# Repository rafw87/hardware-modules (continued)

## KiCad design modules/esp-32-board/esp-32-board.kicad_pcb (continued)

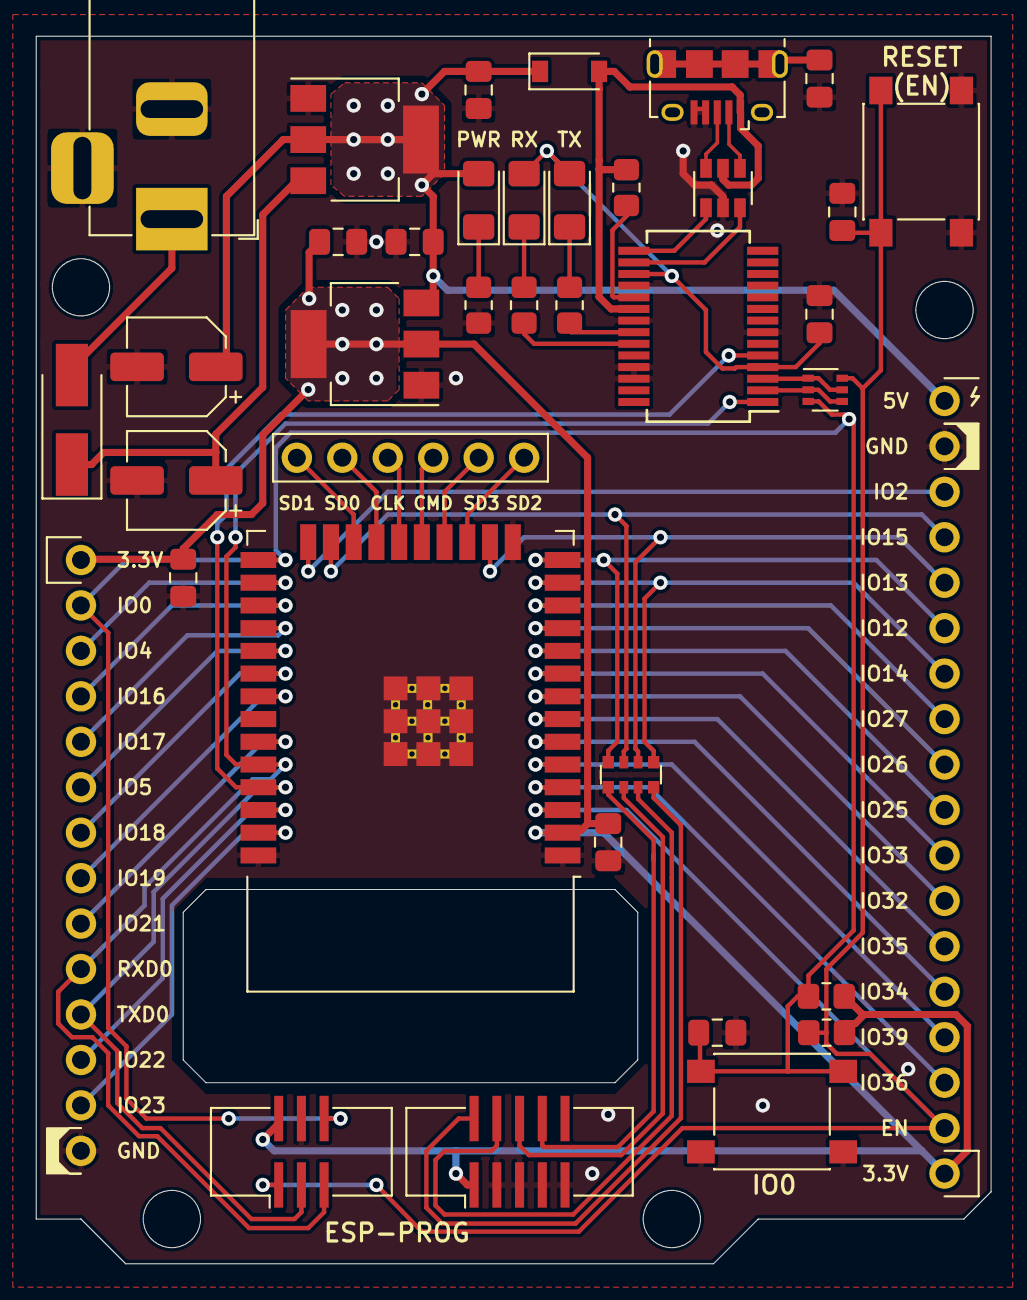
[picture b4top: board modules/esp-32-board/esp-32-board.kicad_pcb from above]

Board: 2 copper layers, 53.4 x 68.6 mm, 39 parts (0 on the bottom side), 57 nets.

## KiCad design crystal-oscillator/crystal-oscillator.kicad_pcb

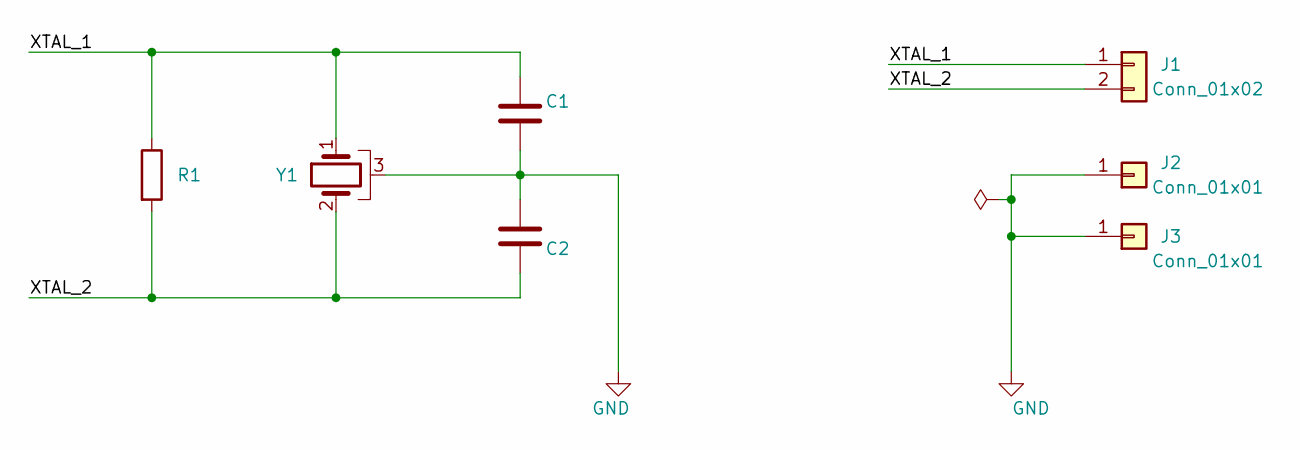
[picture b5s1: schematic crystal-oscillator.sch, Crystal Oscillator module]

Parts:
C1, C2: C; C_Disc_D3.4mm_W2.1mm_P2.50mm
J1: Conn_01x02; PinHeader_1x02_P2.54mm_Vertical
J2, J3: Conn_01x01; PinHeader_1x01_P2.54mm_Vertical-GND
R1: R; R_Axial_DIN0207_L6.3mm_D2.5mm_P7.62mm_Horizontal
Y1: Crystal_GND3; Crystal_C26-LF_D2.1mm_L6.5mm_Horizontal_1EP_style1

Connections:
/XTAL_1: C1.1, J1.1, R1.1, Y1.1
/XTAL_2: C2.2, J1.2, R1.2, Y1.2
GND: C1.2, C2.1, J2.1, J3.1, Y1.3

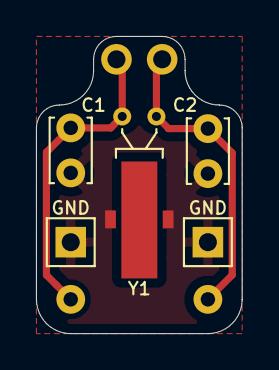
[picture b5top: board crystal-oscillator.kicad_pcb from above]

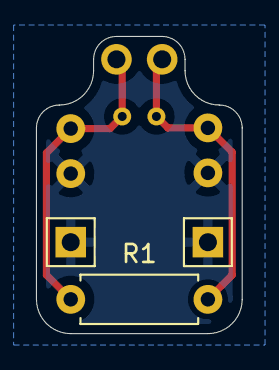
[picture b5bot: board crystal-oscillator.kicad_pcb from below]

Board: 2 copper layers, 11.4 x 16.5 mm, 7 parts (4 on the bottom side), 3 nets.

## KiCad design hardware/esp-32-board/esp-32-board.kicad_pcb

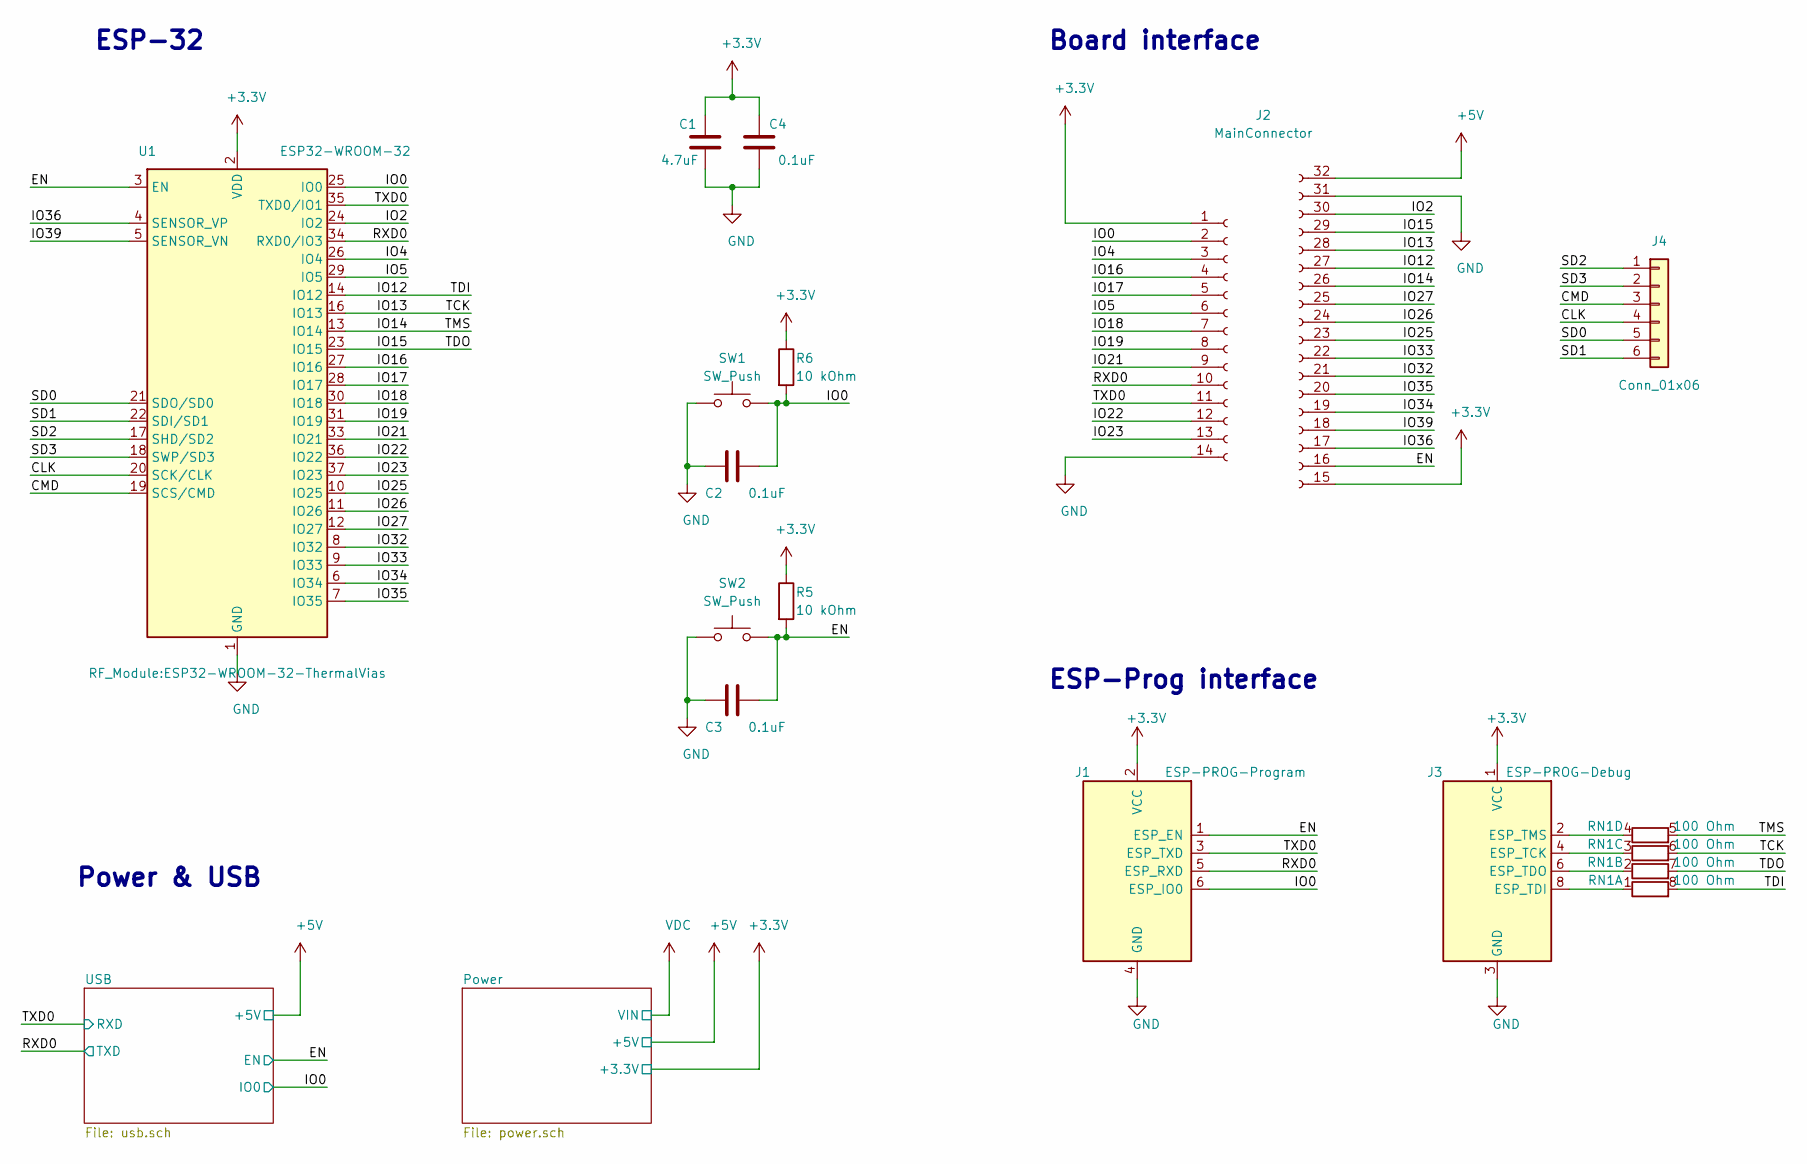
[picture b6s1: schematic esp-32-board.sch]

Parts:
C1: 4.7uF; C_0805_2012Metric_Pad1.18x1.45mm_HandSolder
C2, C3, C4: 0.1uF; C_0805_2012Metric_Pad1.18x1.45mm_HandSolder
J1: ESP-PROG-Program; IDC-Header_2x03_P1.27mm_Vertical_SMD
J2: MainConnector
J3: ESP-PROG-Debug; IDC-Header_2x05_P1.27mm_Vertical_SMD
J4: Conn_01x06; PinSocket_1x06_P2.54mm_Vertical
R5, R6: 10 kOhm; R_0805_2012Metric_Pad1.20x1.40mm_HandSolder
RN1: 100 Ohm; R_Array_Convex_4x0612
SW1, SW2: SW_Push; SW_Push_1P1T_NO_6x6mm_H4.3mm
U1: ESP32-WROOM-32; ESP32-WROOM-32-ThermalVias

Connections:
+3V3: C1.1, C4.1, J1.2 (VCC), J2.1, J2.15, J3.1 (VCC), R5.1, R6.1, U1.2 (VDD); also elsewhere on the board
+5V: J2.32; also elsewhere on the board
/CLK: J4.4, U1.20 (SCK/CLK)
/CMD: J4.3, U1.19 (SCS/CMD)
/EN: C3.2, J1.1 (ESP_EN), J2.16, R5.2, SW2.2, U1.3 (EN); also elsewhere on the board
/IO0: C2.2, J1.6 (ESP_IO0), J2.2, R6.2, SW1.2, U1.25 (IO0); also elsewhere on the board
/IO2: J2.30, U1.24 (IO2)
/IO4: J2.3, U1.26 (IO4)
/IO5: J2.6, U1.29 (IO5)
/IO12: J2.27, RN1.8 (R1.2), U1.14 (IO12)
/IO13: J2.28, RN1.6 (R3.2), U1.16 (IO13)
/IO14: J2.26, RN1.5 (R4.2), U1.13 (IO14)
/IO15: J2.29, RN1.7 (R2.2), U1.23 (IO15)
/IO16: J2.4, U1.27 (IO16)
/IO17: J2.5, U1.28 (IO17)
/IO18: J2.7, U1.30 (IO18)
/IO19: J2.8, U1.31 (IO19)
/IO21: J2.9, U1.33 (IO21)
/IO22: J2.12, U1.36 (IO22)
/IO23: J2.13, U1.37 (IO23)
/IO25: J2.23, U1.10 (IO25)
/IO26: J2.24, U1.11 (IO26)
/IO27: J2.25, U1.12 (IO27)
/IO32: J2.21, U1.8 (IO32)
/IO33: J2.22, U1.9 (IO33)
/IO34: J2.19, U1.6 (IO34)
/IO35: J2.20, U1.7 (IO35)
/IO36: J2.17, U1.4 (SENSOR_VP)
/IO39: J2.18, U1.5 (SENSOR_VN)
/RXD0: J1.5 (ESP_RXD), J2.10, U1.34 (RXD0/IO3); also elsewhere on the board
/SD0: J4.5, U1.21 (SDO/SD0)
/SD1: J4.6, U1.22 (SDI/SD1)
/SD2: J4.1, U1.17 (SHD/SD2)
/SD3: J4.2, U1.18 (SWP/SD3)
/TXD0: J1.3 (ESP_TXD), J2.11, U1.35 (TXD0/IO1); also elsewhere on the board
GND: C1.2, C2.1, C3.1, C4.2, J1.4 (GND), J2.14, J2.31, J3.3 (GND), J3.5 (GND), J3.7 (GND), J3.9 (GND), SW1.1, SW2.1, U1.1 (GND), U1.15 (GND), U1.38 (GND), U1.39 (GND); also elsewhere on the board
unnamed: J3.2 (ESP_TMS), RN1.4 (R4.1)
unnamed: J3.4 (ESP_TCK), RN1.3 (R3.1)
unnamed: J3.6 (ESP_TDO), RN1.2 (R2.1)
unnamed: J3.8 (ESP_TDI), RN1.1 (R1.1)

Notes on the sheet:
Power & USB
ESP-Prog interface
Board interface
ESP-32

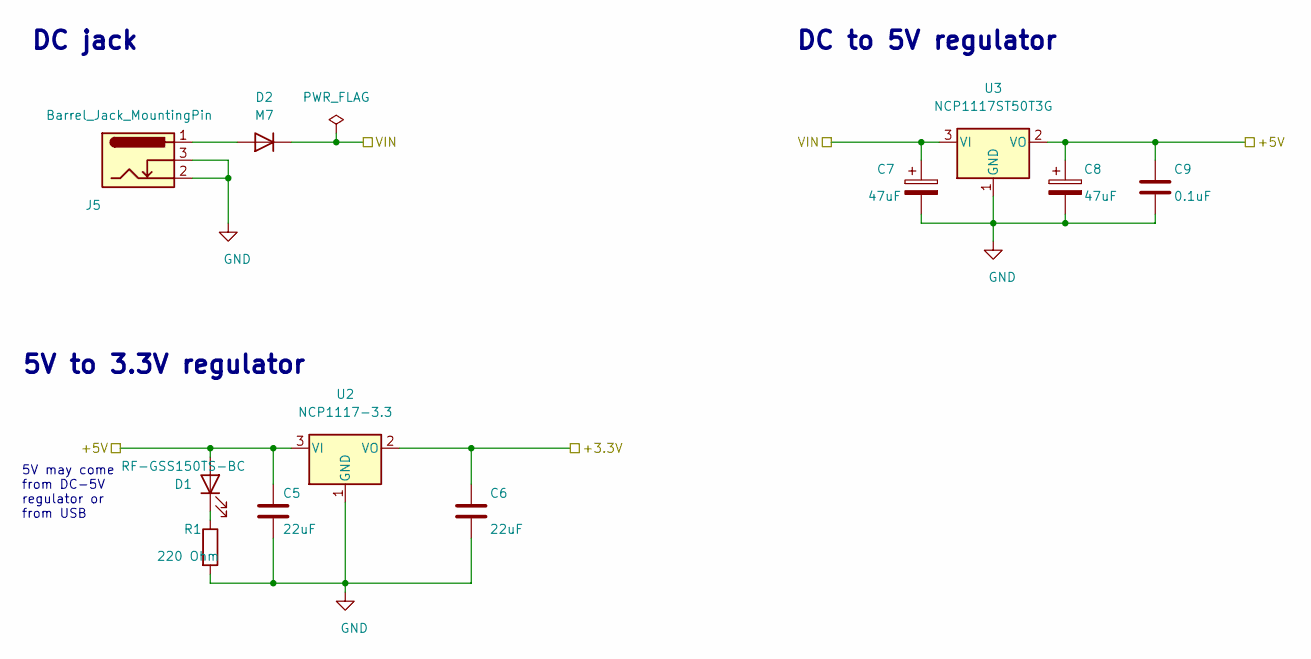
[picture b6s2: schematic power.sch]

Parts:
C5, C6: 22uF; C_0805_2012Metric_Pad1.18x1.45mm_HandSolder
C7, C8: 47uF; CP_Elec_5x5.9
C9: 0.1uF; C_0805_2012Metric_Pad1.18x1.45mm_HandSolder
D1: RF-GSS150TS-BC; LED_1206_3216Metric_Pad1.42x1.75mm_HandSolder
D2: M7; D_SMA_Handsoldering
J5: Barrel_Jack_MountingPin; BarrelJack_CLIFF_FC68148_Horizontal
R1: 220 Ohm; R_0805_2012Metric_Pad1.20x1.40mm_HandSolder
U2: NCP1117-3.3; SOT-223-3_TabPin2
U3: NCP1117ST50T3G; SOT-223-3_TabPin2

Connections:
+3V3: C6.1, U2.2 (VO); also elsewhere on the board
+5V: C5.1, C8.1, C9.1, D1.2 (A), U2.3 (VI), U3.2 (VO); also elsewhere on the board
GND: C5.2, C6.2, C7.2, C8.2, C9.2, J5.2, J5.3, R1.2, U2.1 (GND), U3.1 (GND); also elsewhere on the board
unnamed: D1.1 (K), R1.1
unnamed: D2.2 (A), J5.1
VDC: C7.1, D2.1 (K), U3.3 (VI)

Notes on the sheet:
DC jack
DC to 5V regulator
5V to 3.3V regulator
5V may come from DC-5V regulator or from USB

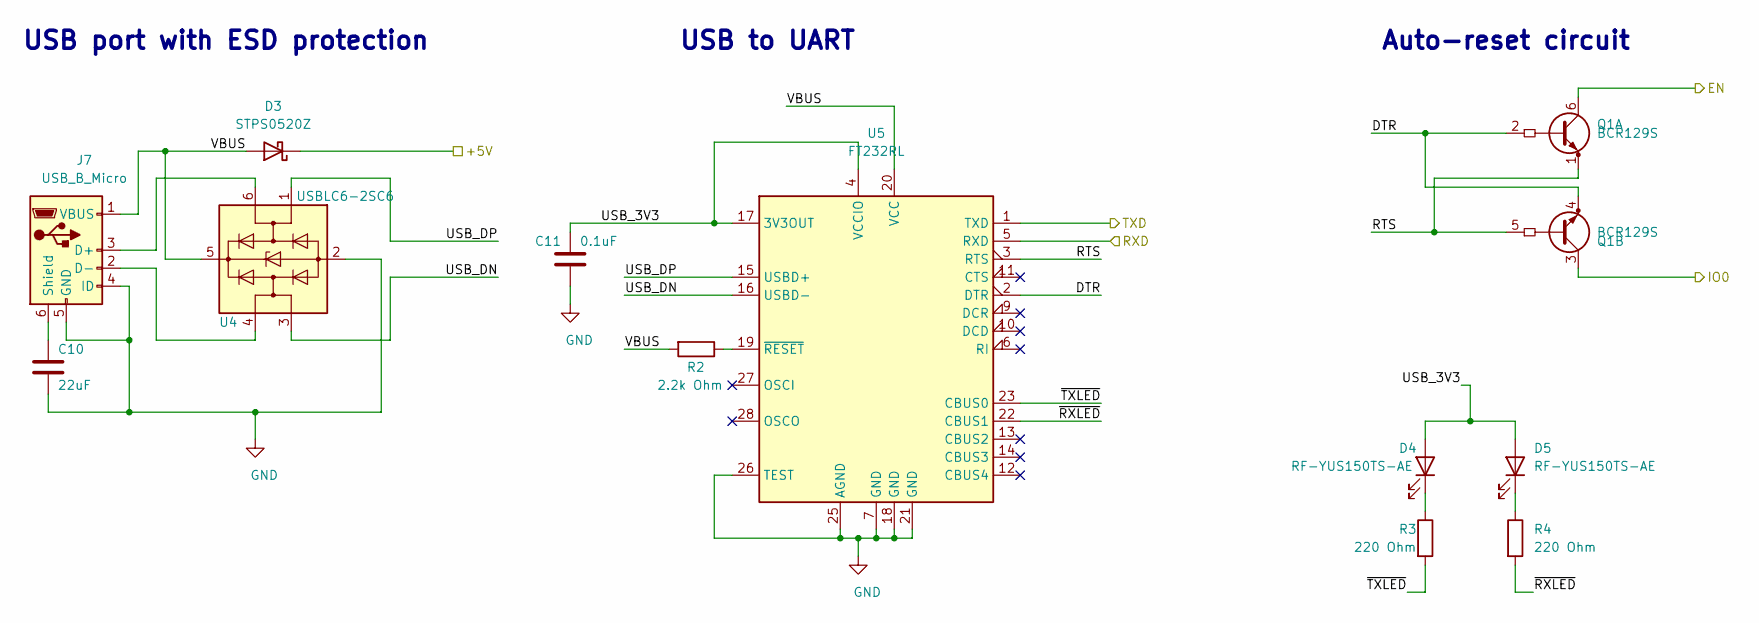
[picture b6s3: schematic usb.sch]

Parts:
C10: 22uF; C_0805_2012Metric_Pad1.18x1.45mm_HandSolder
C11: 0.1uF; C_0805_2012Metric_Pad1.18x1.45mm_HandSolder
D3: STPS0520Z; D_SOD-123
D4, D5: RF-YUS150TS-AE; LED_1206_3216Metric_Pad1.42x1.75mm_HandSolder
J7: USB_B_Micro; USB_Micro-B_Amphenol_10118194_Horizontal
Q1: BCR129S; SOT-363_SC-70-6
R2: 2.2k Ohm; R_0805_2012Metric_Pad1.20x1.40mm_HandSolder
R3, R4: 220 Ohm; R_0805_2012Metric_Pad1.20x1.40mm_HandSolder
U4: USBLC6-2SC6; SOT-23-6
U5: FT232RL; SSOP-28_5.3x10.2mm_P0.65mm

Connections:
+5V: D3.1 (K); also elsewhere on the board
/EN: Q1.6 (C1); also elsewhere on the board
/IO0: Q1.3 (C1); also elsewhere on the board
/RXD0: U5.1 (TXD); also elsewhere on the board
/TXD0: U5.5 (RXD); also elsewhere on the board
/USB/DTR: Q1.2 (B1), Q1.4 (E2), U5.2 (DTR)
/USB/RTS: Q1.1 (E1), Q1.5 (B2), U5.3 (RTS)
/USB/USB_3V3: C11.1, D4.2 (A), D5.2 (A), U5.4 (VCCIO), U5.17 (3V3OUT)
/USB/USB_DN: U4.3 (I/O2), U5.16 (USBD-)
/USB/USB_DP: U4.1 (I/O1), U5.15 (USBD+)
/USB/VBUS: D3.2 (A), J7.1 (VBUS), R2.2, U4.5 (VBUS), U5.20 (VCC)
/USB/~RXLED: R4.2, U5.22 (CBUS1)
/USB/~TXLED: R3.2, U5.23 (CBUS0)
GND: C10.2, C11.2, J7.4 (ID), J7.5 (GND), U4.2 (GND), U5.7 (GND), U5.18 (GND), U5.21 (GND), U5.25 (AGND), U5.26 (TEST); also elsewhere on the board
unnamed: C10.1, J7.6 (Shield)
unnamed: D4.1 (K), R3.1
unnamed: D5.1 (K), R4.1
unnamed: J7.2 (D-), U4.4 (I/O2)
unnamed: J7.3 (D+), U4.6 (I/O1)
unnamed: R2.1, U5.19 (~RESET~)

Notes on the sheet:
USB port with ESD protection
USB to UART
Auto-reset circuit

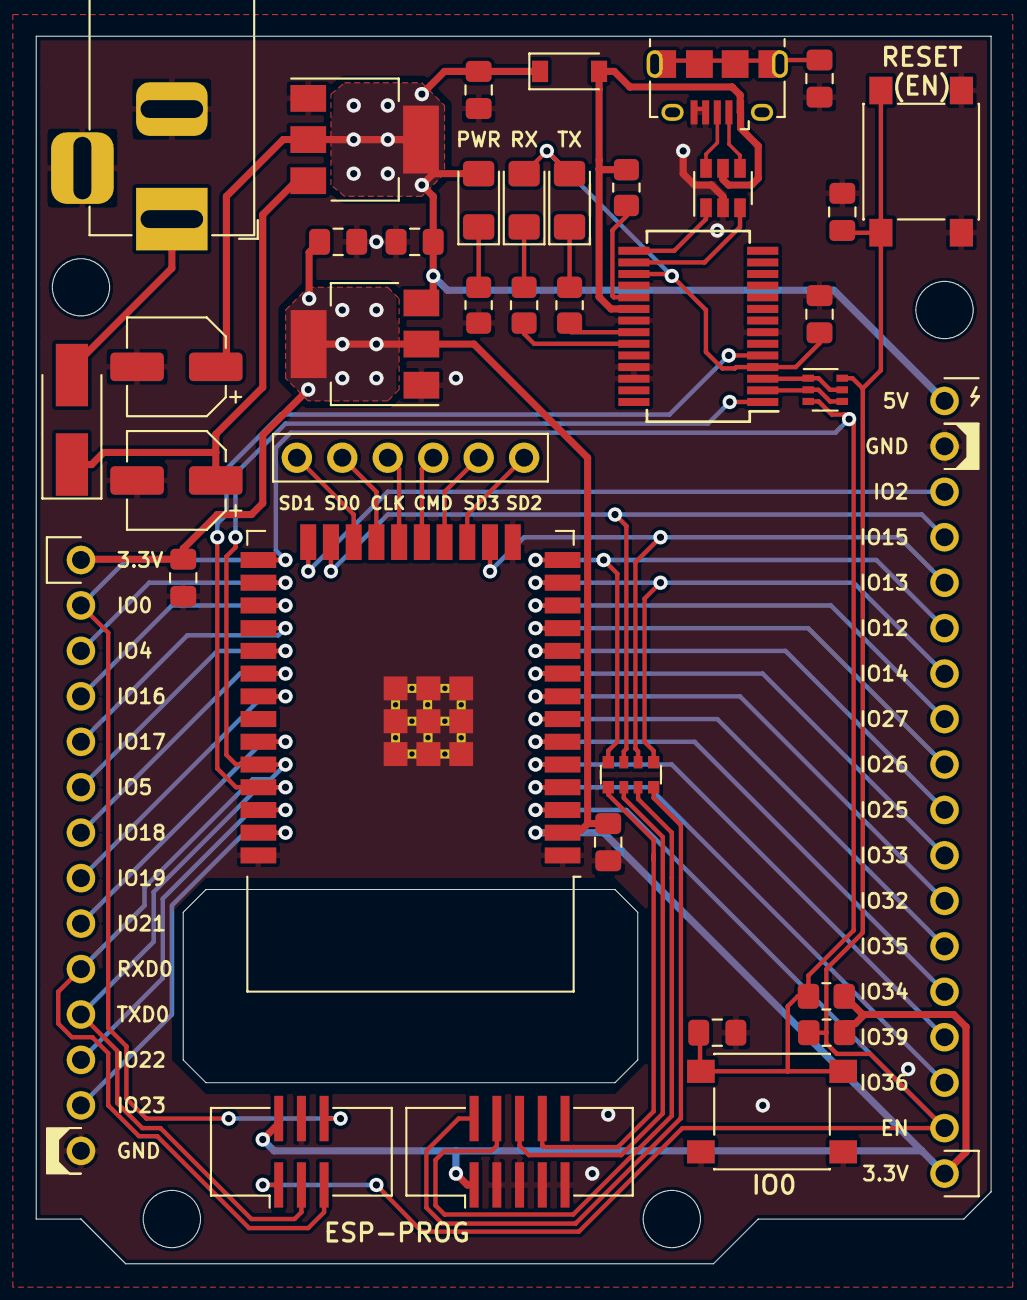
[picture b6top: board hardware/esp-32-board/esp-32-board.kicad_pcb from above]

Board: 2 copper layers, 53.4 x 68.6 mm, 37 parts (0 on the bottom side), 57 nets.

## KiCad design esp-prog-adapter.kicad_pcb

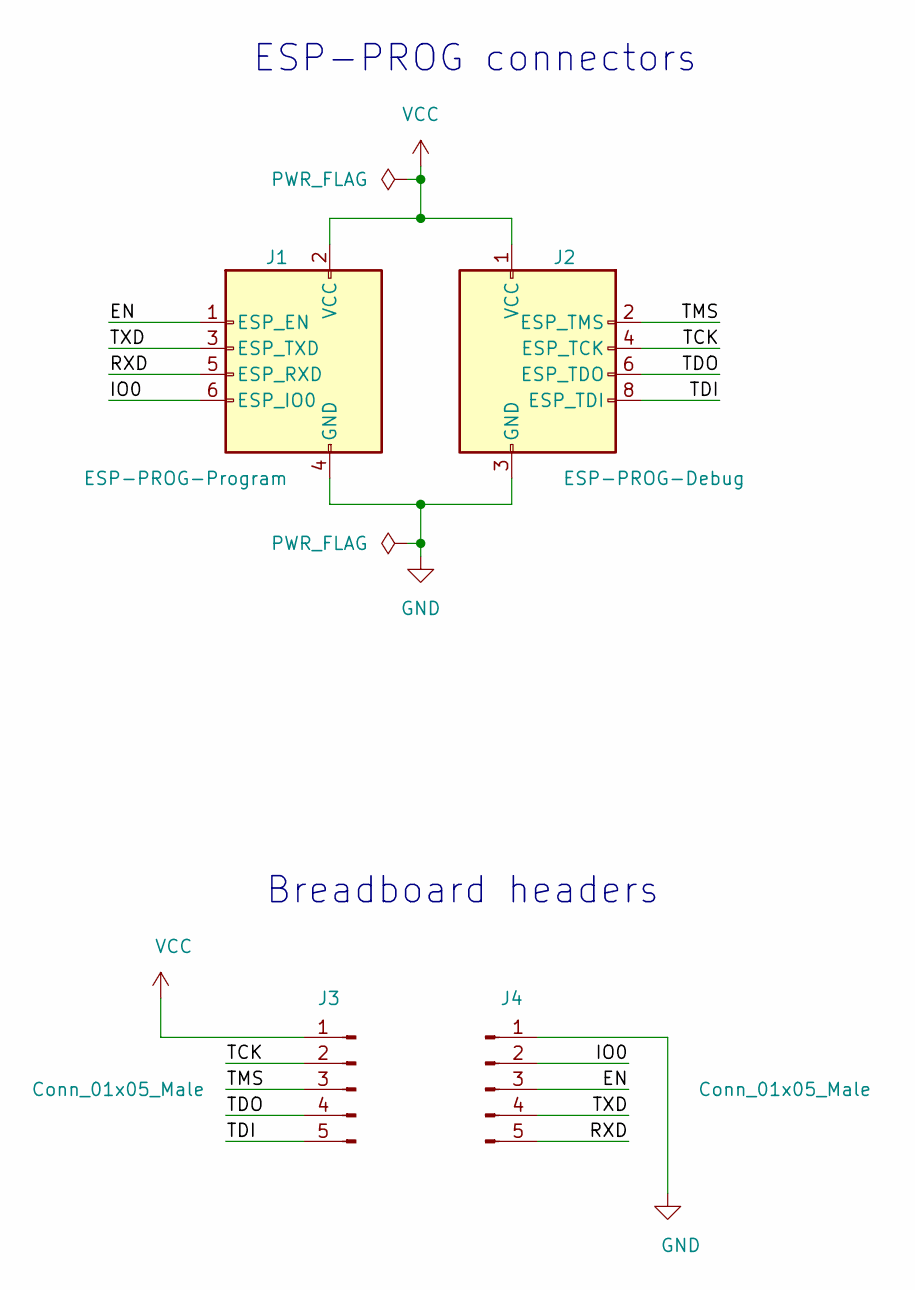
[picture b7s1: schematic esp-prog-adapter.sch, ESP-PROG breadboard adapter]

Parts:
J1: ESP-PROG-Program; IDC-Header_2x03_P1.27mm_Vertical_SMD
J2: ESP-PROG-Debug; IDC-Header_2x05_P1.27mm_Vertical_SMD
J3, J4: Conn_01x05_Male; PinHeader_1x05_P2.54mm_Vertical

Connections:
/EN: J1.1 (ESP_EN), J4.3
/IO0: J1.6 (ESP_IO0), J4.2
/RXD: J1.5 (ESP_RXD), J4.5
/TCK: J2.4 (ESP_TCK), J3.2
/TDI: J2.8 (ESP_TDI), J3.5
/TDO: J2.6 (ESP_TDO), J3.4
/TMS: J2.2 (ESP_TMS), J3.3
/TXD: J1.3 (ESP_TXD), J4.4
GND: J1.4 (GND), J2.3 (GND), J2.5 (GND), J2.7 (GND), J2.9 (GND), J4.1
VCC: J1.2 (VCC), J2.1 (VCC), J3.1

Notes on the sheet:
ESP-PROG connectors
Breadboard headers

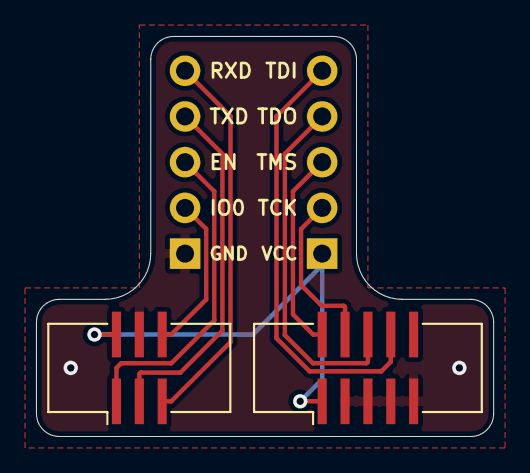
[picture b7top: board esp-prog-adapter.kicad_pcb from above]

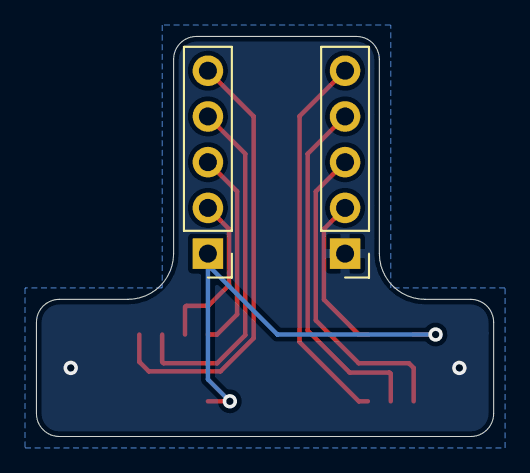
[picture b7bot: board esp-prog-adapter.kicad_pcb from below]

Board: 2 copper layers, 25.4 x 22.2 mm, 4 parts (2 on the bottom side), 10 nets.

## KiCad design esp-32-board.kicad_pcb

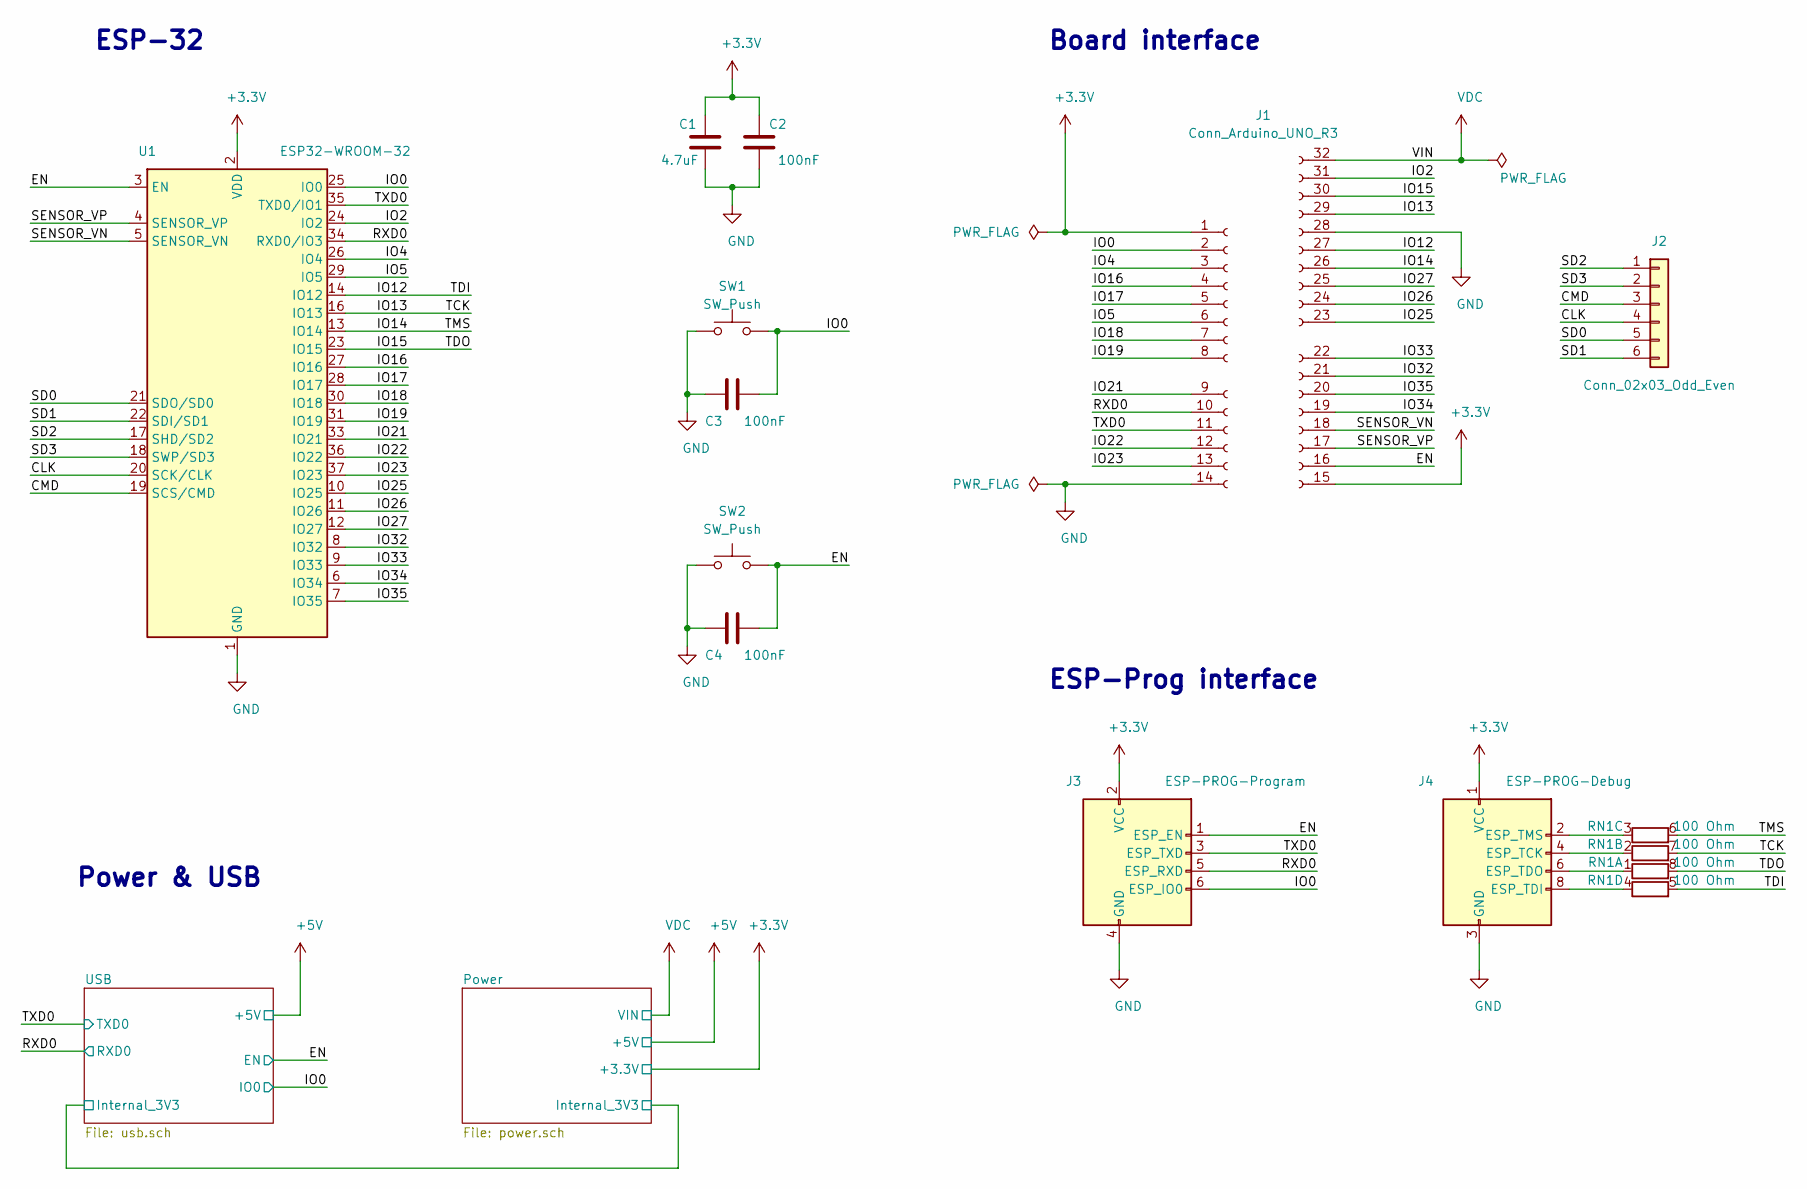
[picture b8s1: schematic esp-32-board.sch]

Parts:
C1: 4.7uF; C_0805_2012Metric_Pad1.18x1.45mm_HandSolder
C2, C3, C4: 100nF; C_0805_2012Metric_Pad1.18x1.45mm_HandSolder
J1: Conn_Arduino_UNO_R3; Arduino_UNO_R3_WithMountingHoles
J2: Conn_02x03_Odd_Even; PinSocket_1x06_P2.54mm_Vertical_SMD_Pin1Left
J3: ESP-PROG-Program; IDC-Header_2x03_P1.27mm_Vertical_SMD
J4: ESP-PROG-Debug; IDC-Header_2x05_P1.27mm_Vertical_SMD
RN1: 100 Ohm; R_Array_Convex_4x1206
SW1, SW2: SW_Push; SW_Push_1P1T_NO_6x6mm_H4.3mm
U1: ESP32-WROOM-32

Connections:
+3V3: C1.1, C2.1, J1.1, J1.15, J3.2 (VCC), J4.1 (VCC), U1.2 (VDD); also elsewhere on the board
/CLK: J2.4, U1.20 (SCK/CLK)
/CMD: J2.3, U1.19 (SCS/CMD)
/EN: C4.2, J1.16, J3.1 (ESP_EN), SW2.2, U1.3 (EN); also elsewhere on the board
/IO0: C3.2, J1.2, J3.6 (ESP_IO0), SW1.2, U1.25 (IO0); also elsewhere on the board
/IO2: J1.31, U1.24 (IO2)
/IO4: J1.3, U1.26 (IO4)
/IO5: J1.6, U1.29 (IO5)
/IO12: J1.27, RN1.5 (R4.2), U1.14 (IO12)
/IO13: J1.29, RN1.7 (R2.2), U1.16 (IO13)
/IO14: J1.26, RN1.6 (R3.2), U1.13 (IO14)
/IO15: J1.30, RN1.8 (R1.2), U1.23 (IO15)
/IO16: J1.4, U1.27 (IO16)
/IO17: J1.5, U1.28 (IO17)
/IO18: J1.7, U1.30 (IO18)
/IO19: J1.8, U1.31 (IO19)
/IO21: J1.9, U1.33 (IO21)
/IO22: J1.12, U1.36 (IO22)
/IO23: J1.13, U1.37 (IO23)
/IO25: J1.23, U1.10 (IO25)
/IO26: J1.24, U1.11 (IO26)
/IO27: J1.25, U1.12 (IO27)
/IO32: J1.21, U1.8 (IO32)
/IO33: J1.22, U1.9 (IO33)
/IO34: J1.19, U1.6 (IO34)
/IO35: J1.20, U1.7 (IO35)
/RXD0: J1.10, J3.5 (ESP_RXD), U1.34 (RXD0/IO3); also elsewhere on the board
/SD0: J2.5, U1.21 (SDO/SD0)
/SD1: J2.6, U1.22 (SDI/SD1)
/SD2: J2.1, U1.17 (SHD/SD2)
/SD3: J2.2, U1.18 (SWP/SD3)
/SENSOR_VN: J1.18, U1.5 (SENSOR_VN)
/SENSOR_VP: J1.17, U1.4 (SENSOR_VP)
/TXD0: J1.11, J3.3 (ESP_TXD), U1.35 (TXD0/IO1); also elsewhere on the board
GND: C1.2, C2.2, C3.1, C4.1, J1.14, J1.28, J3.4 (GND), J4.3 (GND), J4.5 (GND), J4.7 (GND), J4.9 (GND), SW1.1, SW2.1, U1.1 (GND), U1.15 (GND), U1.38 (GND), U1.39 (GND); also elsewhere on the board
unnamed: J4.2 (ESP_TMS), RN1.3 (R3.1)
unnamed: J4.4 (ESP_TCK), RN1.2 (R2.1)
unnamed: J4.6 (ESP_TDO), RN1.1 (R1.1)
unnamed: J4.8 (ESP_TDI), RN1.4 (R4.1)
VDC: J1.32; also elsewhere on the board

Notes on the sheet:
Power & USB
ESP-Prog interface
Board interface
ESP-32

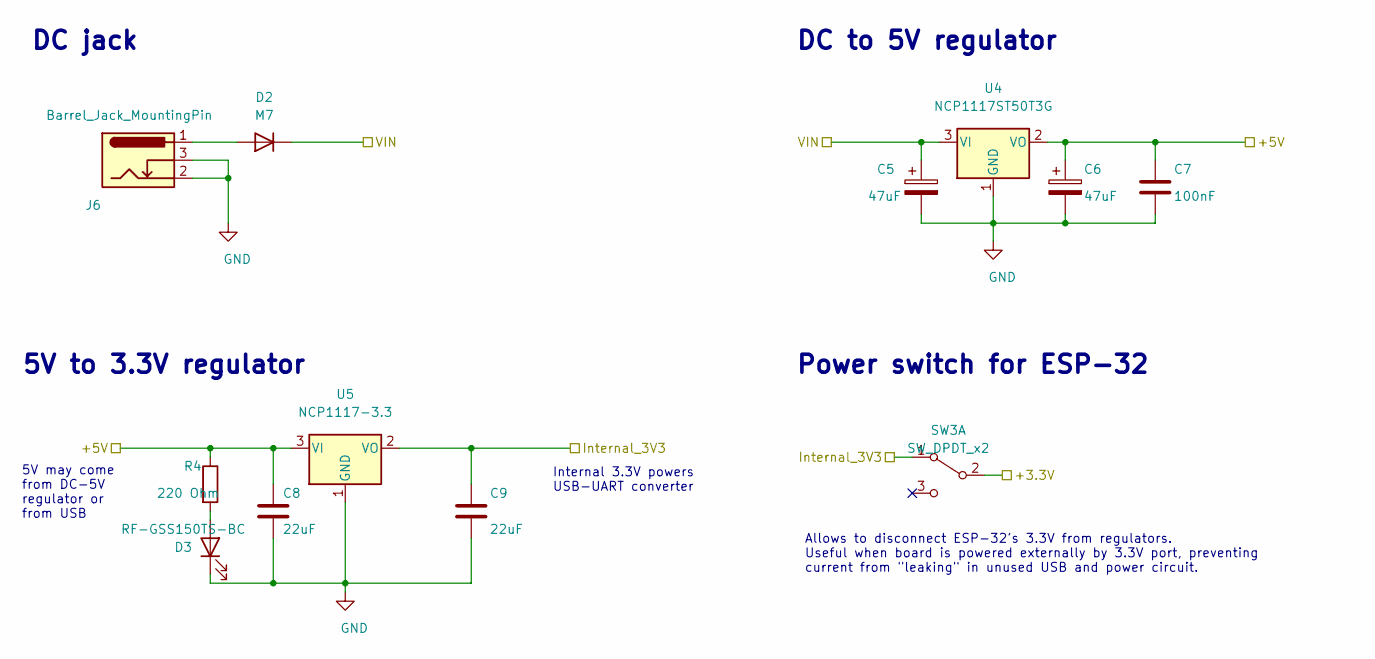
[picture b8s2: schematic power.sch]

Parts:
C5, C6: 47uF; CP_Elec_5x5.9
C7: 100nF; C_0805_2012Metric_Pad1.18x1.45mm_HandSolder
C8, C9: 22uF; C_0805_2012Metric_Pad1.18x1.45mm_HandSolder
D2: M7; D_SMA_Handsoldering
D3: RF-GSS150TS-BC; LED_1206_3216Metric_Pad1.42x1.75mm_HandSolder
J6: Barrel_Jack_MountingPin; BarrelJack_Lumberg_1613-21_Horizontal
R4: 220 Ohm; R_0805_2012Metric_Pad1.20x1.40mm_HandSolder
SW3: SW_DPDT_x2; Nidec_CL-SB-22B-0X
U4: NCP1117ST50T3G; SOT-223-3_TabPin2
U5: NCP1117-3.3; SOT-223-3_TabPin2

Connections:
+3V3: SW3.2 (B); also elsewhere on the board
+5V: C6.1, C7.1, C8.1, R4.1, U4.2 (VO), U5.3 (VI); also elsewhere on the board
/Power/Internal_3V3: C9.1, SW3.1 (A), U5.2 (VO); also elsewhere on the board
GND: C5.2, C6.2, C7.2, C8.2, C9.2, D3.1 (K), J6.2, J6.3, U4.1 (GND), U5.1 (GND); also elsewhere on the board
unnamed: D2.2 (A), J6.1
unnamed: D3.2 (A), R4.2
VDC: C5.1, D2.1 (K), U4.3 (VI); also elsewhere on the board

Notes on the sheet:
DC jack
DC to 5V regulator
5V to 3.3V regulator
5V may come from DC-5V regulator or from USB
Internal 3.3V powers USB-UART converter
Power switch for ESP-32
Allows to disconnect ESP-32's 3.3V from regulators. Useful when board is powered externally by 3.3V port, preventing current from "leaking" in unused USB and power circuit.

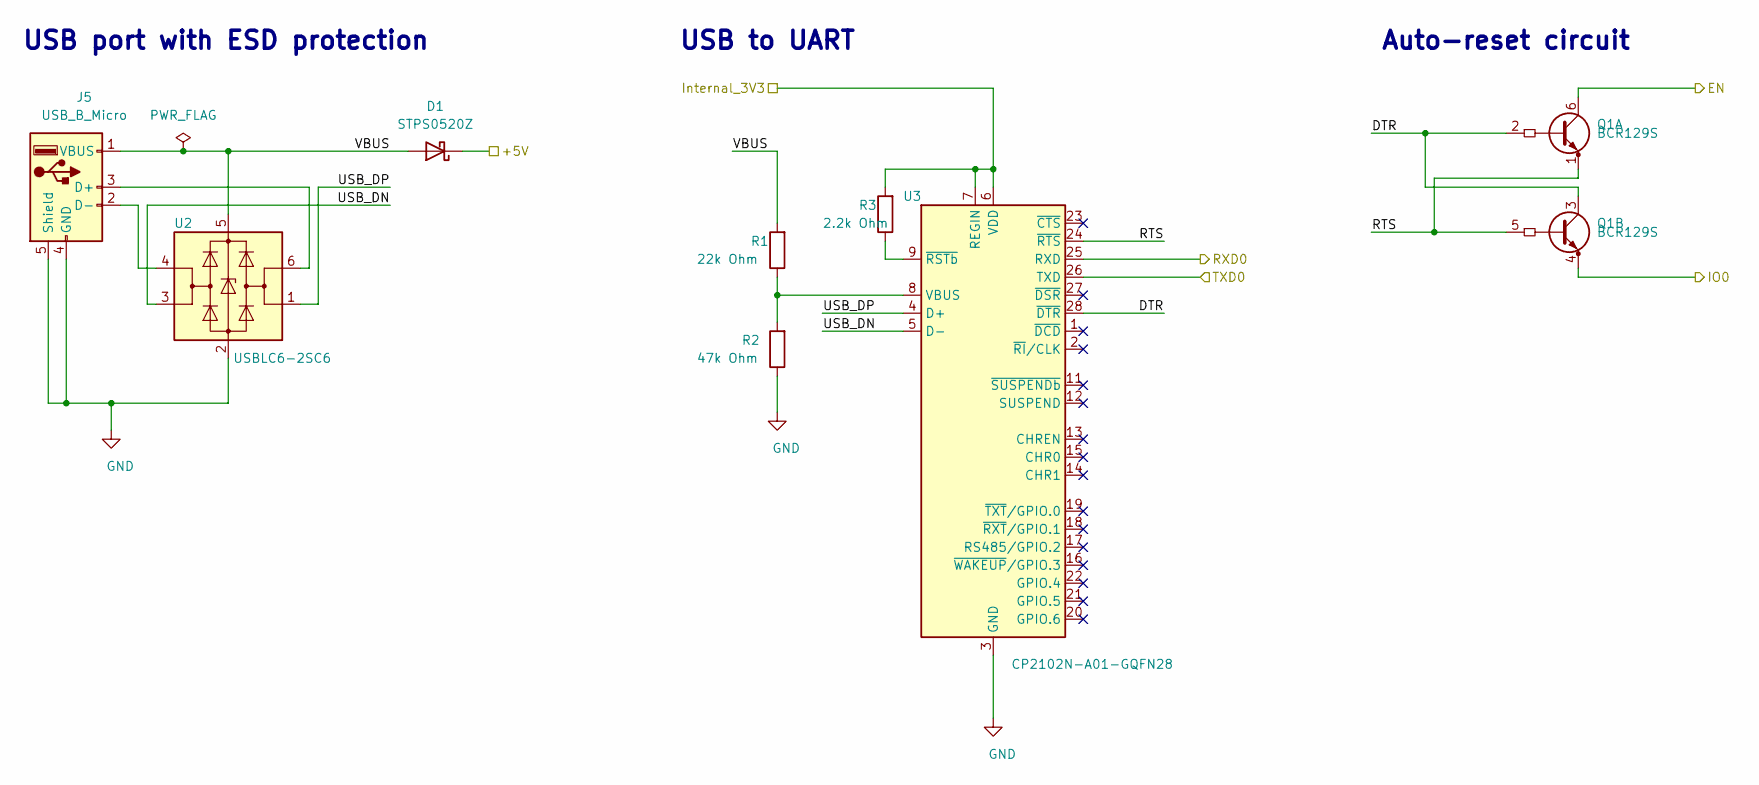
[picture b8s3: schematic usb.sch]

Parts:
D1: STPS0520Z; D_SOD-123
J5: USB_B_Micro; USB_Micro-B_Molex_47346-0001
Q1: BCR129S; SOT-363_SC-70-6
R1: 22k Ohm; R_0805_2012Metric_Pad1.20x1.40mm_HandSolder
R2: 47k Ohm; R_0805_2012Metric_Pad1.20x1.40mm_HandSolder
R3: 2.2k Ohm; R_0805_2012Metric_Pad1.20x1.40mm_HandSolder
U2: USBLC6-2SC6; SOT-23-6
U3: CP2102N-A01-GQFN28; QFN-28-1EP_5x5mm_P0.5mm_EP3.35x3.35mm

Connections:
+5V: D1.1 (K); also elsewhere on the board
/EN: Q1.6 (C1); also elsewhere on the board
/IO0: Q1.4 (E2); also elsewhere on the board
/Power/Internal_3V3: R3.2, U3.6 (VDD), U3.7 (REGIN); also elsewhere on the board
/RXD0: U3.25 (RXD); also elsewhere on the board
/TXD0: U3.26 (TXD); also elsewhere on the board
/USB/DTR: Q1.2 (B1), Q1.3 (C1), U3.28 (~DTR)
/USB/RTS: Q1.1 (E1), Q1.5 (B2), U3.24 (~RTS)
/USB/USB_DN: U2.3 (I/O2), U3.5 (D-)
/USB/USB_DP: U2.1 (I/O1), U3.4 (D+)
/USB/VBUS: D1.2 (A), J5.1 (VBUS), R1.2, U2.5 (VBUS)
GND: J5.4 (GND), J5.5 (Shield), R2.1, U2.2 (GND), U3.3 (GND), U3.29 (GND); also elsewhere on the board
unnamed: J5.2 (D-), U2.4 (I/O2)
unnamed: J5.3 (D+), U2.6 (I/O1)
unnamed: R1.1, R2.2, U3.8 (VBUS)
unnamed: R3.1, U3.9 (~RSTb)

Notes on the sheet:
USB port with ESD protection
USB to UART
Auto-reset circuit

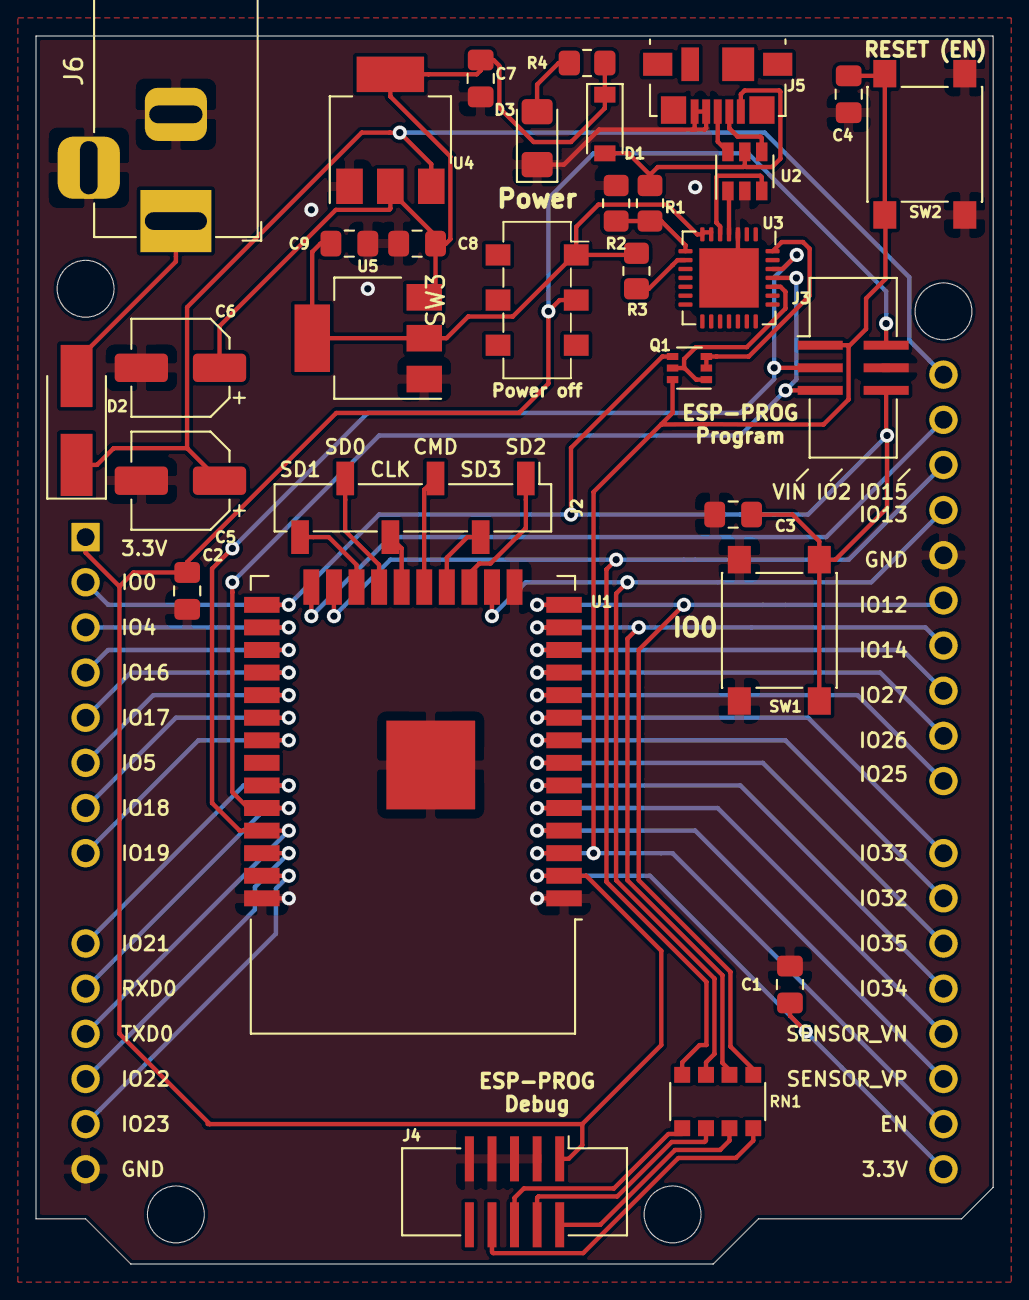
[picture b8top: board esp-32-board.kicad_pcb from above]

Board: 2 copper layers, 53.8 x 69.1 mm, 32 parts (1 on the bottom side), 53 nets.
